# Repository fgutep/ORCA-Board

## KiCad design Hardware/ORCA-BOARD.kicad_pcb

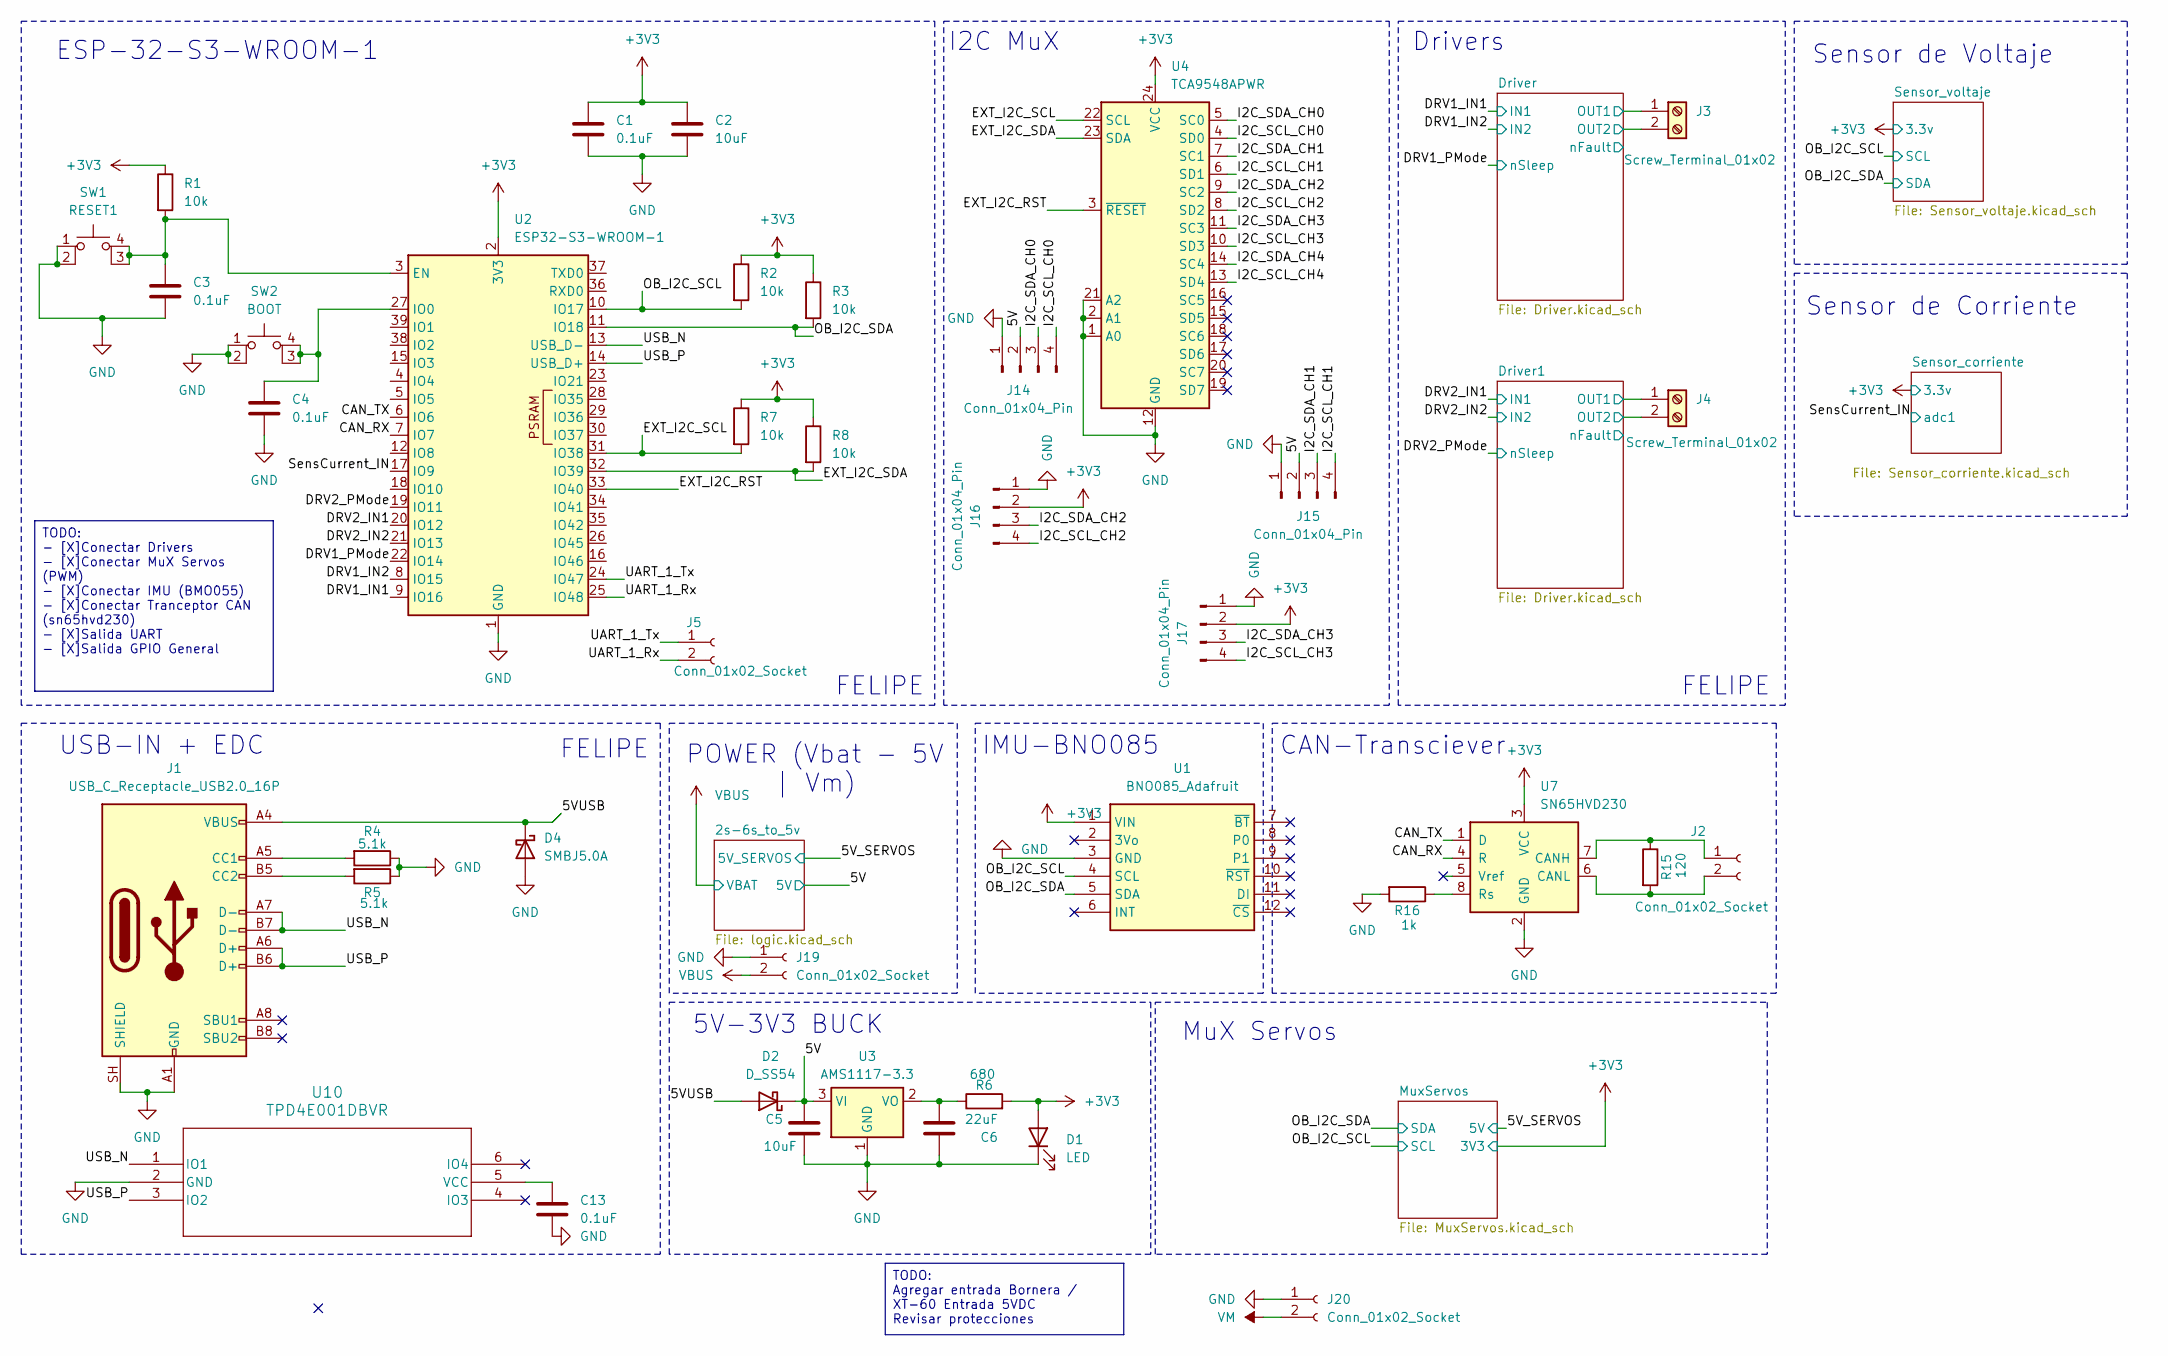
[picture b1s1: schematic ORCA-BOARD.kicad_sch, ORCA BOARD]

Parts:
C1, C3, C4, C13: 0.1uF; C_0603_1608Metric_Pad1.08x0.95mm_HandSolder
C2, C5: 10uF; C_1206_3216Metric_Pad1.33x1.80mm_HandSolder
C6: 22uF; C_1206_3216Metric_Pad1.33x1.80mm_HandSolder
D1: LED; LED_0603_1608Metric_Pad1.05x0.95mm_HandSolder
D2: D_SS54; D_SMA_Handsoldering
D4: SMBJ5.0A; D_SMB
J1: USB_C_Receptacle_USB2.0_16P; USB_C_Receptacle_GCT_USB4105-xx-A_16P_TopMnt_Horizontal
J2: Conn_01x02_Socket; JST_ZH_B2B-ZR_1x02_P1.50mm_Vertical
J3, J4: Screw_Terminal_01x02; TerminalBlock_Phoenix_MPT-0,5-2-2.54_1x02_P2.54mm_Horizontal
J5: Conn_01x02_Socket; JST_EH_B2B-EH-A_1x02_P2.50mm_Vertical
J14, J15, J16, J17: Conn_01x04_Pin; JST_EH_B4B-EH-A_1x04_P2.50mm_Vertical
J19, J20: Conn_01x02_Socket; AMASS_XT60-F_1x02_P7.20mm_Vertical
R1, R2, R3, R7, R8: 10k; LED_0603_1608Metric_Pad1.05x0.95mm_HandSolder
R4, R5: 5.1k; LED_0603_1608Metric_Pad1.05x0.95mm_HandSolder
R6: 680; LED_0603_1608Metric_Pad1.05x0.95mm_HandSolder
R15: 120; LED_0603_1608Metric_Pad1.05x0.95mm_HandSolder
R16: 1k; LED_0603_1608Metric_Pad1.05x0.95mm_HandSolder
SW1: RESET1; SW_SPST_B3S-1000_1_4_labels
SW2: BOOT; SW_SPST_B3S-1000_1_4_labels
U1: BNO085_Adafruit
U2: ESP32-S3-WROOM-1
U3: AMS1117-3.3; SOT-223-3_TabPin2
U4: TCA9548APWR; TSSOP-24_4.4x7.8mm_P0.65mm
U7: SN65HVD230; SOIC-8_3.9x4.9mm_P1.27mm
U10: TPD4E001DBVR; DBV6-M

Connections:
+3V3: C1.1, C2.1, D1.2 (A), J16.2, J17.2, R1.1, R2.1, R3.1, R6.2, R7.1, R8.1, U1.1 (VIN), U2.2 (3V3), U4.24 (VCC), U7.3 (VCC); also elsewhere on the board
/5V: C5.1, D2.1 (K), J14.2, J15.2, U3.3 (VI); also elsewhere on the board
/5VUSB: D2.2 (A), D4.1 (K), J1.A4 (VBUS), J1.A9 (VBUS), J1.B4 (VBUS), J1.B9 (VBUS)
/CAN_RX: U2.7 (IO7), U7.4 (R)
/CAN_TX: U2.6 (IO6), U7.1 (D)
/DRV1_IN1: U2.9 (IO16); also elsewhere on the board
/DRV1_IN2: U2.8 (IO15); also elsewhere on the board
/DRV1_PMode: U2.22 (IO14); also elsewhere on the board
/DRV2_IN1: U2.20 (IO12); also elsewhere on the board
/DRV2_IN2: U2.21 (IO13); also elsewhere on the board
/DRV2_PMode: U2.19 (IO11); also elsewhere on the board
/Driver1/OUT1: J4.1; also elsewhere on the board
/Driver1/OUT2: J4.2; also elsewhere on the board
/Driver/OUT1: J3.1; also elsewhere on the board
/Driver/OUT2: J3.2; also elsewhere on the board
/EXT_I2C_RST: U2.33 (IO40), U4.3 (~RESET)
/EXT_I2C_SCL: R7.2, U2.31 (IO38), U4.22 (SCL)
/EXT_I2C_SDA: R8.2, U2.32 (IO39), U4.23 (SDA)
/I2C_SCL_CH0: J14.4, U4.4 (SD0)
/I2C_SCL_CH1: J15.4, U4.6 (SD1)
/I2C_SCL_CH2: J16.4, U4.8 (SD2)
/I2C_SCL_CH3: J17.4, U4.10 (SD3)
/I2C_SCL_CH4: U4.13 (SD4)
/I2C_SDA_CH0: J14.3, U4.5 (SC0)
/I2C_SDA_CH1: J15.3, U4.7 (SC1)
/I2C_SDA_CH2: J16.3, U4.9 (SC2)
/I2C_SDA_CH3: J17.3, U4.11 (SC3)
/I2C_SDA_CH4: U4.14 (SC4)
/OB_I2C_SCL: R2.2, U1.4 (SCL), U2.10 (IO17); also elsewhere on the board
/OB_I2C_SDA: R3.2, U1.5 (SDA), U2.11 (IO18); also elsewhere on the board
/SensCurrent_IN: U2.17 (IO9); also elsewhere on the board
/UART_1_Rx: J5.2, U2.25 (IO48)
/UART_1_Tx: J5.1, U2.24 (IO47)
/USB_N: J1.A7 (D-), J1.B7 (D-), U2.13 (USB_D-), U10.1 (IO1)
/USB_P: J1.A6 (D+), J1.B6 (D+), U2.14 (USB_D+), U10.3 (IO2)
GND: C1.2, C2.2, C3.2, C4.1, C5.2, C6.1, C13.2, D1.1 (K), D4.2 (A), J1.A1 (GND), J1.A12 (GND), J1.B1 (GND), J1.B12 (GND), J1.SH (SHIELD), J14.1, J15.1, J16.1, J17.1, J19.1, J20.1, R4.1, R5.1, R16.2, SW1.1, SW1.2, SW2.1, SW2.2, U1.3 (GND), U2.1 (GND), U2.40 (GND), U2.41 (GND), U3.1 (GND), U4.1 (A0), U4.2 (A1), U4.12 (GND), U4.21 (A2), U7.2 (GND), U10.2 (GND); also elsewhere on the board
unnamed: J1.A5 (CC1), R4.2
unnamed: J1.B5 (CC2), R5.2
unnamed: J2.1, R15.1, U7.7 (CANH)
unnamed: J2.2, R15.2, U7.6 (CANL)
unnamed: C3.1, R1.2, SW1.3 (K), SW1.4 (A), U2.3 (EN)
unnamed: C4.2, SW2.3 (K), SW2.4 (A), U2.27 (IO0)
unnamed: C6.2, R6.1, U3.2 (VO)
unnamed: R16.1, U7.8 (Rs)
unnamed: C13.1, U10.5 (VCC)
VBUS: J19.2; also elsewhere on the board
VM: J20.2; also elsewhere on the board

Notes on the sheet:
FELIPE
Drivers
USB-IN + EDC
ESP-32-S3-WROOM-1
5V-3V3 BUCK
MuX Servos
Sensor de Corriente
I2C MuX
Sensor de Voltaje
POWER (Vbat - 5V | Vm)
CAN-Transciever
IMU-BNO085
TODO: Agregar entrada Bornera / XT-60 Entrada 5VDC Revisar protecciones
TODO: - [X]Conectar Drivers - [X]Conectar MuX Servos (PWM) - [X]Conectar IMU (BMO055) - [X]Conectar Tranceptor CAN (sn65hvd230) - [X]Salida UART - [X]Salida GPIO General

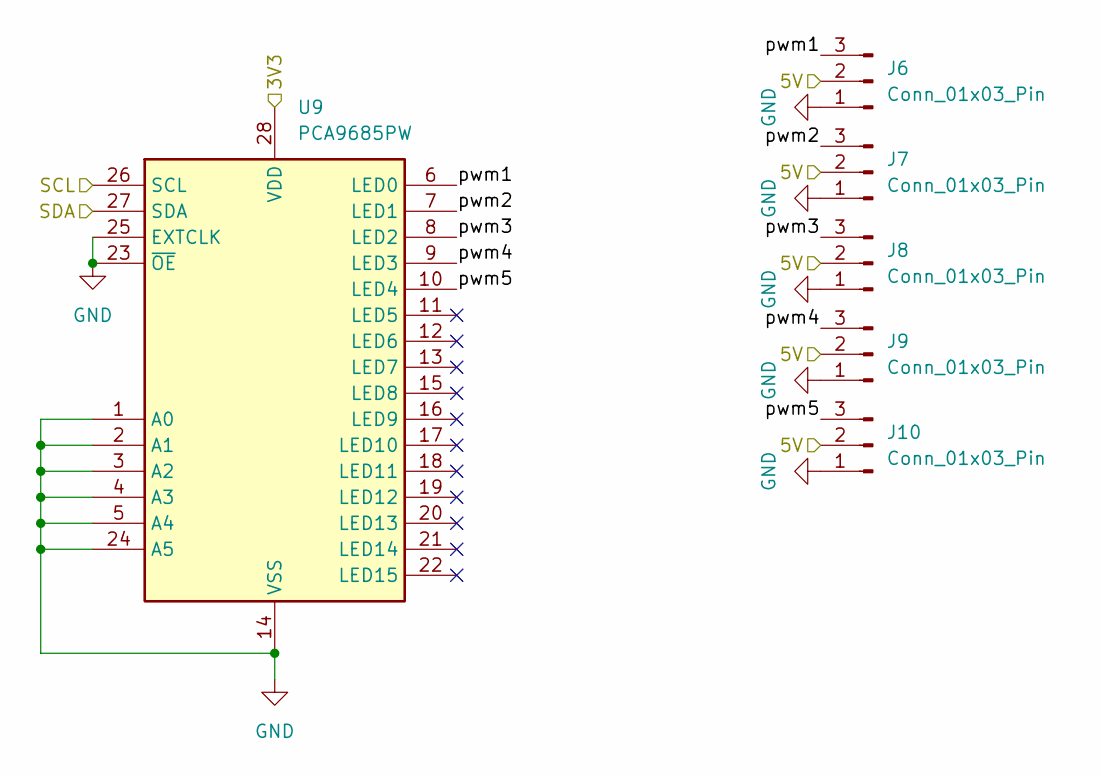
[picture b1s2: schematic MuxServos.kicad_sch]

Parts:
J6, J7, J8, J9, J10: Conn_01x03_Pin; PinHeader_1x03_P2.54mm_Vertical
U9: PCA9685PW; TSSOP-28_4.4x9.7mm_P0.65mm

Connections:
+3V3: U9.28 (VDD); also elsewhere on the board
/5V_SERVOS: J6.2, J7.2, J8.2, J9.2, J10.2; also elsewhere on the board
/MuxServos/pwm1: J6.3, U9.6 (LED0)
/MuxServos/pwm2: J7.3, U9.7 (LED1)
/MuxServos/pwm3: J8.3, U9.8 (LED2)
/MuxServos/pwm4: J9.3, U9.9 (LED3)
/MuxServos/pwm5: J10.3, U9.10 (LED4)
/OB_I2C_SCL: U9.26 (SCL); also elsewhere on the board
/OB_I2C_SDA: U9.27 (SDA); also elsewhere on the board
GND: J6.1, J7.1, J8.1, J9.1, J10.1, U9.1 (A0), U9.2 (A1), U9.3 (A2), U9.4 (A3), U9.5 (A4), U9.14 (VSS), U9.23 (~OE), U9.24 (A5), U9.25 (EXTCLK); also elsewhere on the board

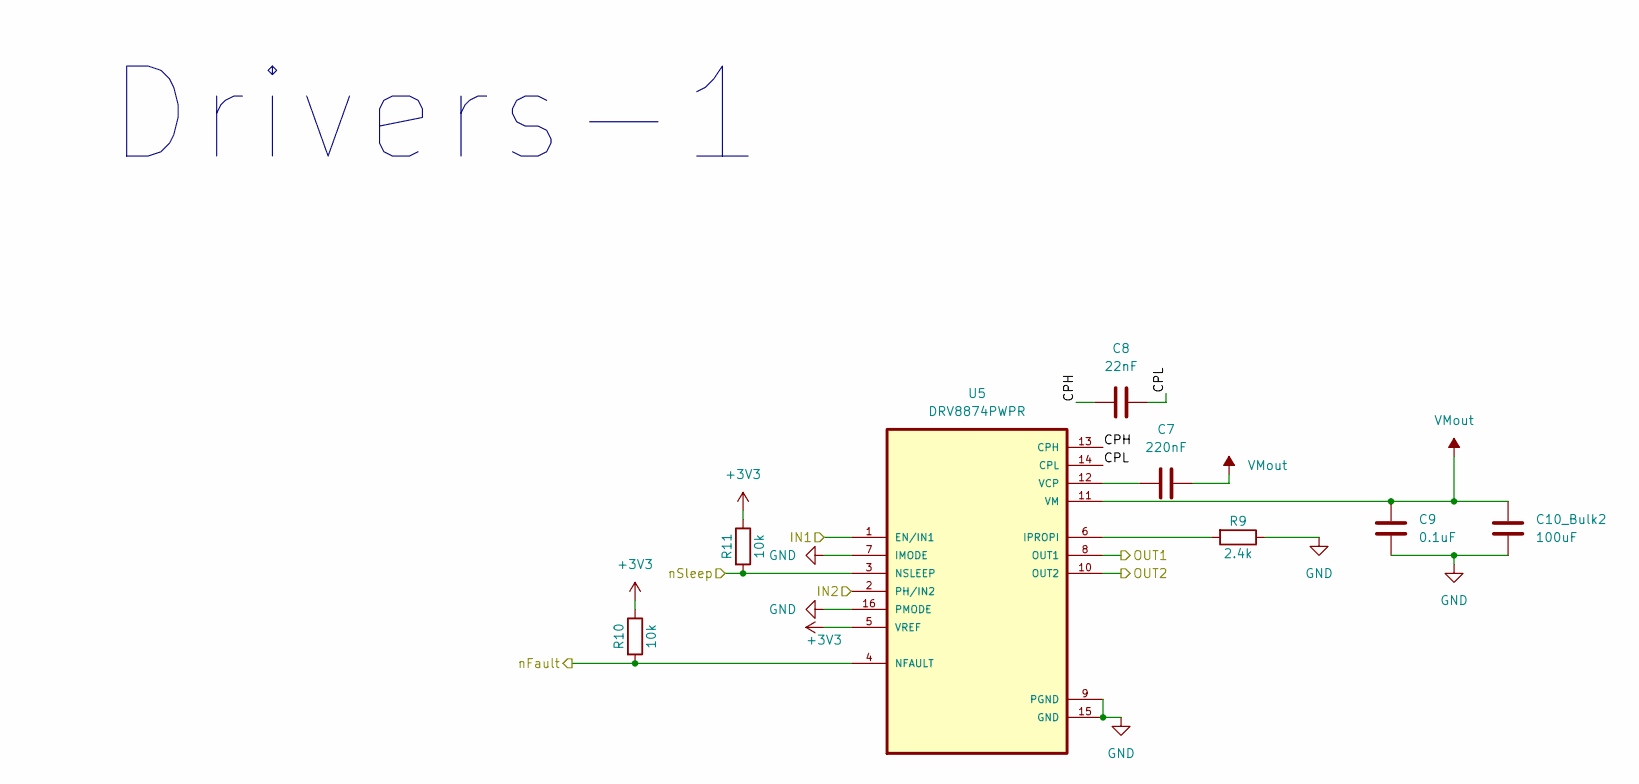
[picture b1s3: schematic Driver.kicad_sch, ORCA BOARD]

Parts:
C7: 220nF; C_0603_1608Metric_Pad1.08x0.95mm_HandSolder
C8: 22nF; C_0603_1608Metric_Pad1.08x0.95mm_HandSolder
C9: 0.1uF; C_0603_1608Metric_Pad1.08x0.95mm_HandSolder
C10_Bulk2: 100uF; CP_Elec_10x10.5
R9: 2.4k; R_0603_1608Metric_Pad0.98x0.95mm_HandSolder
R10, R11: 10k; R_0603_1608Metric_Pad0.98x0.95mm_HandSolder
U5: DRV8874PWPR; SOP65P640X120-17N

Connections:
+3V3: R10.1, R11.1, U5.5 (VREF); also elsewhere on the board
/DRV1_IN1: U5.1 (EN/IN1); also elsewhere on the board
/DRV1_IN2: U5.2 (PH/IN2); also elsewhere on the board
/DRV1_PMode: R11.2, U5.3 (NSLEEP); also elsewhere on the board
/Driver/CPH: C8.2, U5.13 (CPH)
/Driver/CPL: C8.1, U5.14 (CPL)
/Driver/OUT1: U5.8 (OUT1); also elsewhere on the board
/Driver/OUT2: U5.10 (OUT2); also elsewhere on the board
/Driver/nFault: R10.2, U5.4 (NFAULT)
GND: C9.2, C10_Bulk2.2, R9.1, U5.7 (IMODE), U5.9 (PGND), U5.15 (GND), U5.16 (PMODE); also elsewhere on the board
unnamed: R9.2, U5.6 (IPROPI)
unnamed: C7.1, U5.12 (VCP)
VMout: C7.2, C9.1, C10_Bulk2.1, U5.11 (VM); also elsewhere on the board

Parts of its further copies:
C10: 22nF; C_0603_1608Metric_Pad1.08x0.95mm_HandSolder
C10_Bulk1: 100uF; CP_Elec_10x10.5
C11: 220nF; C_0603_1608Metric_Pad1.08x0.95mm_HandSolder
C12: 0.1uF; C_0603_1608Metric_Pad1.08x0.95mm_HandSolder
R12, R13: 10k; R_0603_1608Metric_Pad0.98x0.95mm_HandSolder
R14: 2.4k; R_0603_1608Metric_Pad0.98x0.95mm_HandSolder
U6: DRV8874PWPR; SOP65P640X120-17N

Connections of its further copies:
+3V3: R12.1, R13.1, U6.5 (VREF); also elsewhere on the board
/DRV2_IN1: U6.1 (EN/IN1); also elsewhere on the board
/DRV2_IN2: U6.2 (PH/IN2); also elsewhere on the board
/DRV2_PMode: R13.2, U6.3 (NSLEEP); also elsewhere on the board
/Driver1/CPH: C10.2, U6.13 (CPH)
/Driver1/CPL: C10.1, U6.14 (CPL)
/Driver1/OUT1: U6.8 (OUT1); also elsewhere on the board
/Driver1/OUT2: U6.10 (OUT2); also elsewhere on the board
/Driver1/nFault: R12.2, U6.4 (NFAULT)
GND: C10_Bulk1.2, C12.2, R14.1, U6.7 (IMODE), U6.9 (PGND), U6.15 (GND), U6.16 (PMODE); also elsewhere on the board
unnamed: R14.2, U6.6 (IPROPI)
unnamed: C11.1, U6.12 (VCP)
VMout: C10_Bulk1.1, C11.2, C12.1, U6.11 (VM); also elsewhere on the board

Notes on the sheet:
Drivers-1

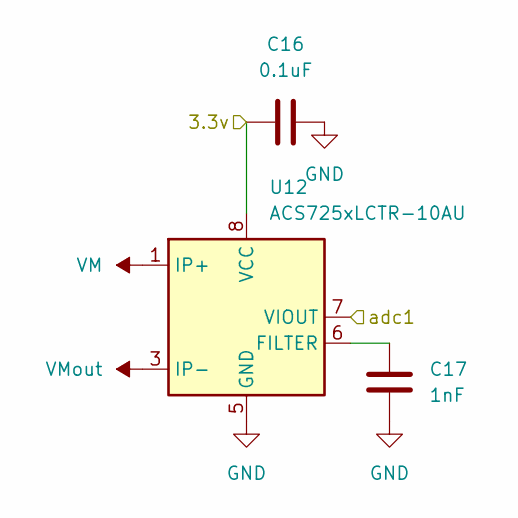
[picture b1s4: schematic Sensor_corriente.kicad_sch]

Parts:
C16: 0.1uF; C_0603_1608Metric_Pad1.08x0.95mm_HandSolder
C17: 1nF; C_0603_1608Metric_Pad1.08x0.95mm_HandSolder
U12: ACS725xLCTR-10AU; SOIC-8_3.9x4.9mm_P1.27mm

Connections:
+3V3: C16.1, U12.8 (VCC); also elsewhere on the board
/SensCurrent_IN: U12.7 (VIOUT); also elsewhere on the board
GND: C16.2, C17.2, U12.5 (GND); also elsewhere on the board
unnamed: C17.1, U12.6 (FILTER)
VM: U12.1 (IP+), U12.2 (IP+); also elsewhere on the board
VMout: U12.3 (IP-), U12.4 (IP-); also elsewhere on the board

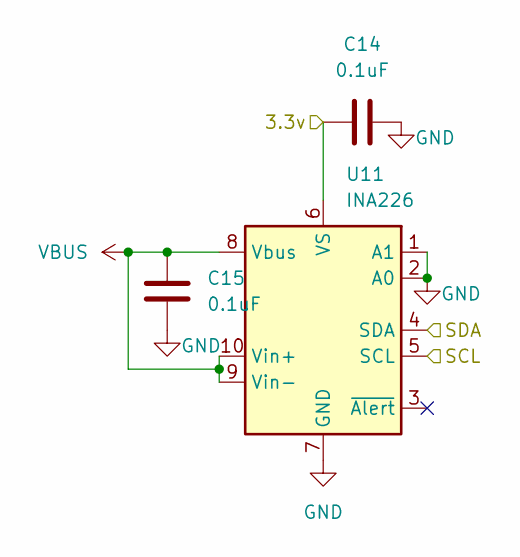
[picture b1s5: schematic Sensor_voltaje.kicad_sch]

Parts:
C14, C15: 0.1uF; C_0603_1608Metric_Pad1.08x0.95mm_HandSolder
U11: INA226; TSSOP-10_3x3mm_P0.5mm

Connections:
+3V3: C14.1, U11.6 (VS); also elsewhere on the board
/OB_I2C_SCL: U11.5 (SCL); also elsewhere on the board
/OB_I2C_SDA: U11.4 (SDA); also elsewhere on the board
GND: C14.2, C15.1, U11.1 (A1), U11.2 (A0), U11.7 (GND); also elsewhere on the board
VBUS: C15.2, U11.8 (Vbus), U11.9 (Vin-), U11.10 (Vin+); also elsewhere on the board

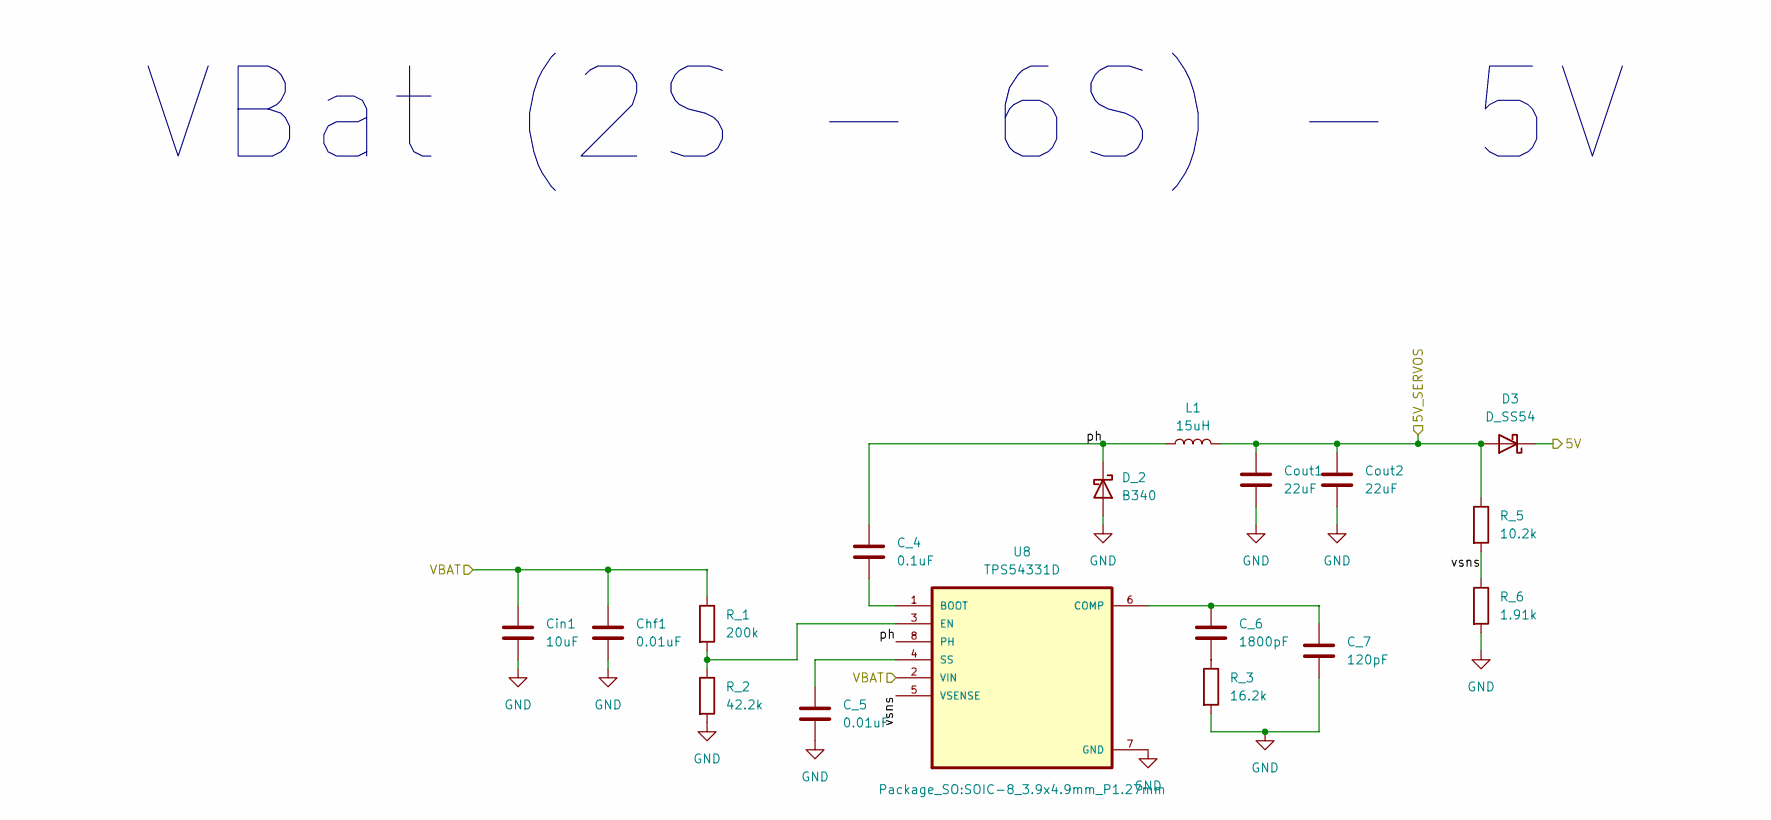
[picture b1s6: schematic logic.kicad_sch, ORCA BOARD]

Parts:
C_4: 0.1uF; C_0603_1608Metric_Pad1.08x0.95mm_HandSolder
C_5: 0.01uF; C_0603_1608Metric_Pad1.08x0.95mm_HandSolder
C_6: 1800pF; C_0603_1608Metric_Pad1.08x0.95mm_HandSolder
C_7: 120pF; C_0603_1608Metric_Pad1.08x0.95mm_HandSolder
Chf1: 0.01uF; C_0603_1608Metric_Pad1.08x0.95mm_HandSolder
Cin1: 10uF; C_1206_3216Metric_Pad1.33x1.80mm_HandSolder
Cout1, Cout2: 22uF; C_1206_3216Metric_Pad1.33x1.80mm_HandSolder
D3: D_SS54; D_SMA_Handsoldering
D_2: B340; D_SMC
L1: 15uH; L_7.3x7.3_H3.5
R_1: 200k; R_0603_1608Metric_Pad0.98x0.95mm_HandSolder
R_2: 42.2k; R_0603_1608Metric_Pad0.98x0.95mm_HandSolder
R_3: 16.2k; R_0603_1608Metric_Pad0.98x0.95mm_HandSolder
R_5: 10.2k; R_0603_1608Metric_Pad0.98x0.95mm_HandSolder
R_6: 1.91k; R_0603_1608Metric_Pad0.98x0.95mm_HandSolder
U8: TPS54331D; SOIC-8_3.9x4.9mm_P1.27mm

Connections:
/2s-6s_to_5v/ph: C_4.1, D_2.1 (K), L1.1, U8.8 (PH)
/2s-6s_to_5v/vsns: R_5.2, R_6.1, U8.5 (VSENSE)
/5V: D3.1 (K); also elsewhere on the board
/5V_SERVOS: Cout1.1, Cout2.1, D3.2 (A), L1.2, R_5.1; also elsewhere on the board
GND: C_5.2, C_7.2, Chf1.2, Cin1.2, Cout1.2, Cout2.2, D_2.2 (A), R_2.2, R_3.2, R_6.2, U8.7 (GND); also elsewhere on the board
unnamed: C_6.2, R_3.1
unnamed: C_4.2, U8.1 (BOOT)
unnamed: C_6.1, C_7.1, U8.6 (COMP)
unnamed: R_1.2, R_2.1, U8.3 (EN)
unnamed: C_5.1, U8.4 (SS)
VBUS: Chf1.1, Cin1.1, R_1.1, U8.2 (VIN); also elsewhere on the board

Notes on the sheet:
VBat (2S - 6S) - 5V

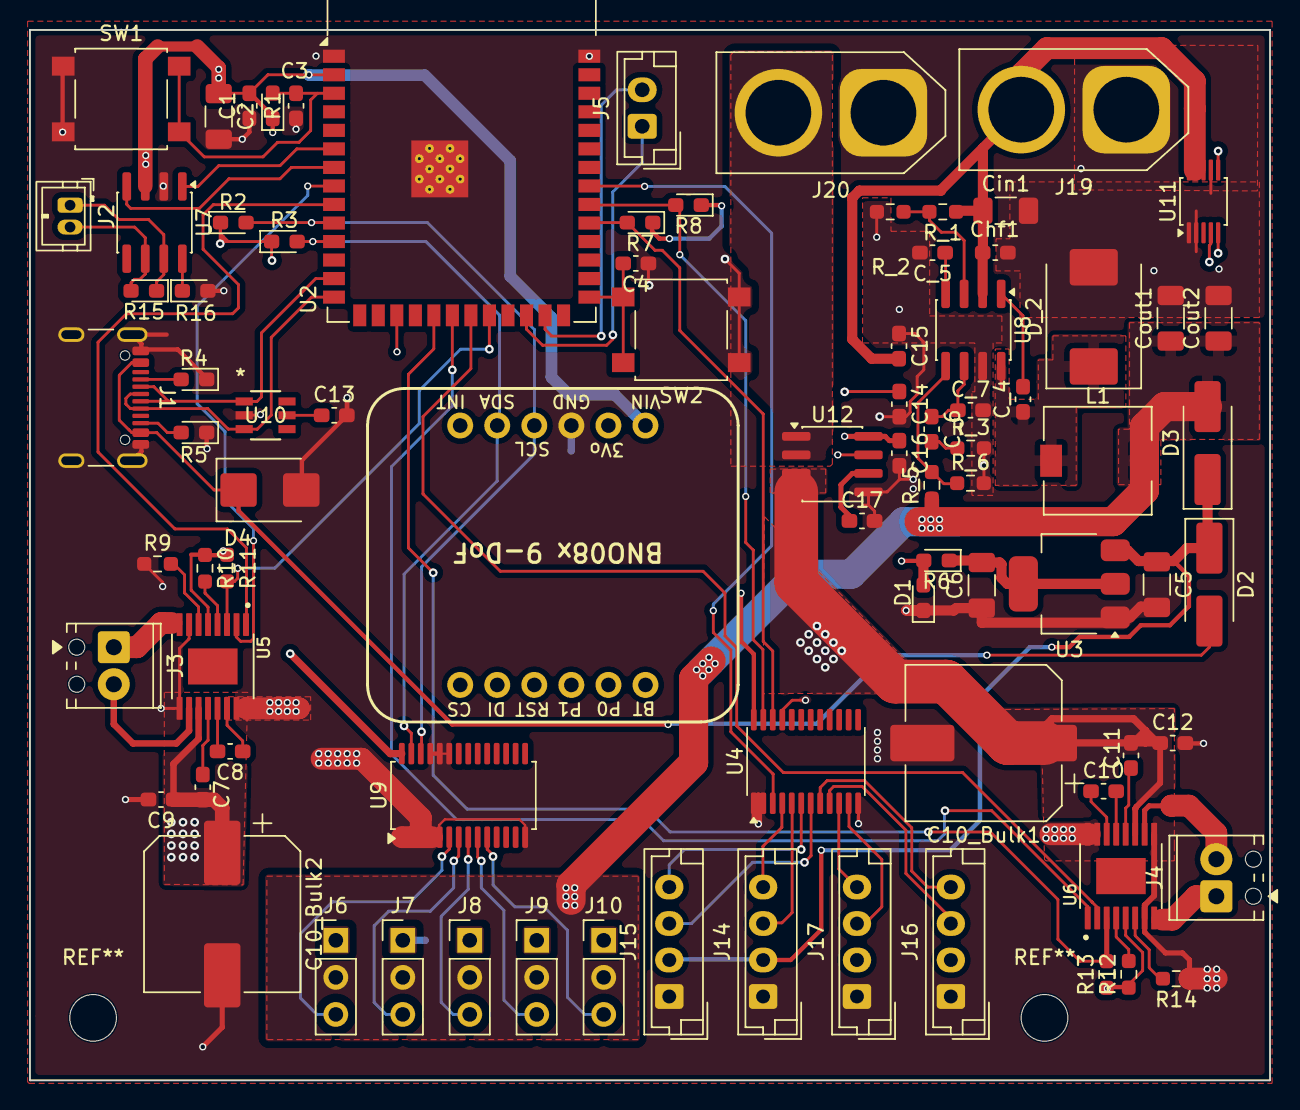
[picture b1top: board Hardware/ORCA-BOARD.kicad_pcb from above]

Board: 4 copper layers, 85.0 x 72.0 mm, 84 parts (0 on the bottom side), 70 nets.

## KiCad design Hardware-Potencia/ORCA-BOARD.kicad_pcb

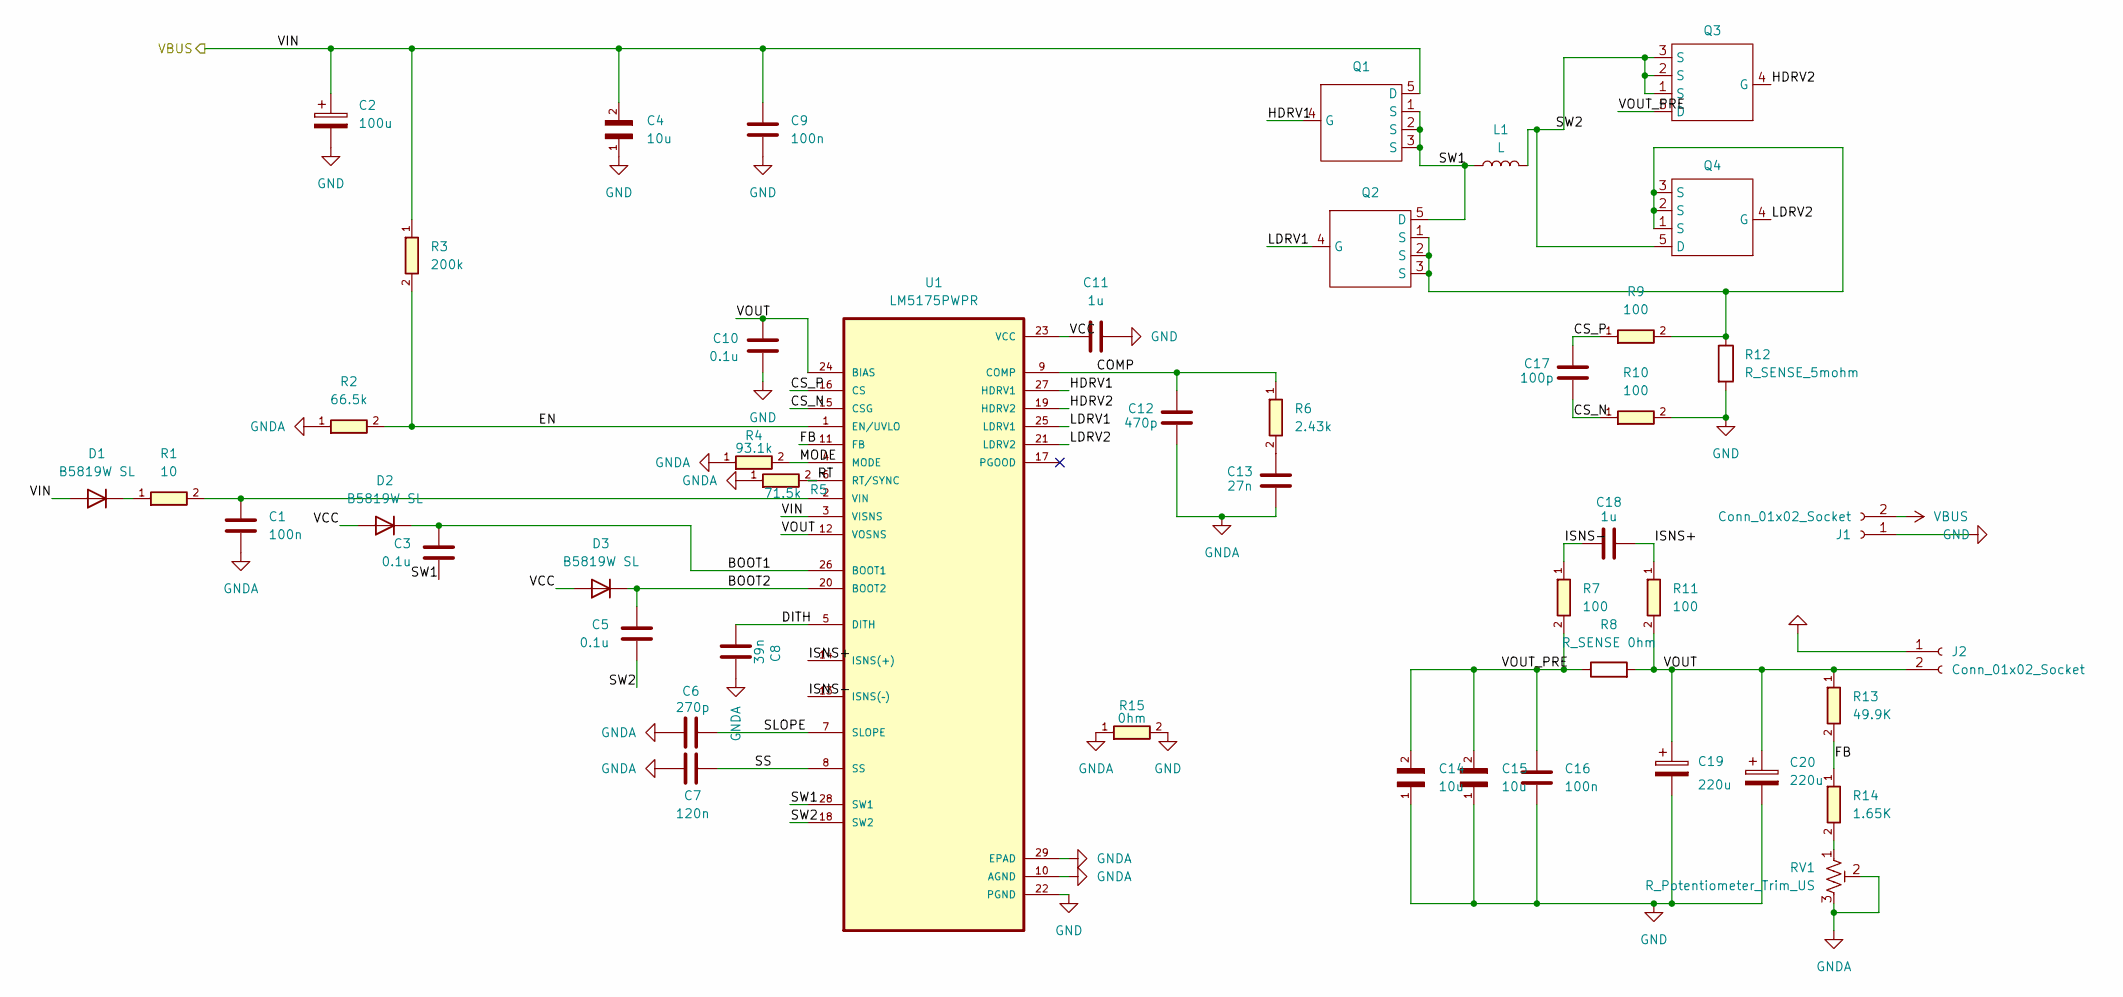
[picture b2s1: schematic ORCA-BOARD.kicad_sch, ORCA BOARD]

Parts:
C1: 100n; 0603
C2: 100u; CP_Radial_D8.0mm_P3.50mm
C3, C5, C10: 0.1u; 0603
C4, C14, C15: 10u; CAPC3225X280N
C6: 270p; 0603
C7: 120n; 0603
C8: 39n; 0603
C9, C16: 100n; CAPC3225X280N
C11, C18: 1u; CAPC2012X100N
C12: 470p; 0603
C13: 27n; 0603
C17: 100p; 0603
C19, C20: 220u; CP_Radial_D8.0mm_P3.50mm
D1, D2, D3: B5819W SL; D_SOD-123
J1, J2: Conn_01x02_Socket; AMASS_XT60-F_1x02_P7.20mm_Vertical
L1: L; L_Pulse_PA4344
Q1, Q2, Q3, Q4: LFPAK56
R1: 10; 0603
R2: 66.5k; 0603
R3: 200k; 0603
R4: 93.1k; 0603
R5: 71.5k; 0603
R6: 2.43k; 0603
R7, R9, R10, R11: 100; 0603
R8: R_SENSE 0hm; RES_1-2176421-2
R12: R_SENSE_5mohm; R_2512_Kelvin_TLRP
R13: 49.9K; 0603
R14: 1.65K; 0603
R15: 0hm; 0603
RV1: R_Potentiometer_Trim_US; Potentiometer_Bourns_3296W_Vertical
U1: LM5175PWPR; LM5175PWP

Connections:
/BOOT1: C3.1, D2.1 (K), U1.26 (BOOT1)
/BOOT2: C5.1, D3.1 (K), U1.20 (BOOT2)
/COMP: C12.2, R6.1, U1.9 (COMP)
/CS_N: C17.1, R10.1, U1.15 (CSG)
/CS_P: C17.2, R9.1, U1.16 (CS)
/DITH: C8.2, U1.5 (DITH)
/EN: R2.2, R3.2, U1.1 (EN/UVLO)
/FB: R13.2, R14.1, U1.11 (FB)
/HDRV1: Q1.4 (G), U1.27 (HDRV1)
/HDRV2: Q3.4 (G), U1.19 (HDRV2)
/ISNS+: C18.2, R11.1, U1.14 (ISNS(+))
/ISNS-: C18.1, R7.1, U1.13 (ISNS(–))
/LDRV1: Q2.4 (G), U1.25 (LDRV1)
/LDRV2: Q4.4 (G), U1.21 (LDRV2)
/MODE: R4.2, U1.4 (MODE)
/RT: R5.2, U1.6 (RT/SYNC)
/SLOPE: C6.2, U1.7 (SLOPE)
/SS: C7.2, U1.8 (SS)
/SW1: C3.2, L1.1, Q1.1 (S), Q1.2 (S), Q1.3 (S), Q2.5 (D), U1.28 (SW1)
/SW2: C5.2, L1.2, Q3.1 (S), Q3.2 (S), Q3.3 (S), Q4.5 (D), U1.18 (SW2)
/VCC: C11.1, D2.2 (A), D3.2 (A), U1.23 (VCC)
/VOUT: C10.1, C19.1, C20.1, J2.2, R8.2, R11.2, R13.1, U1.12 (VOSNS), U1.24 (BIAS)
/VOUT_PRE: C14.2, C15.2, C16.1, Q3.5 (D), R7.2, R8.1
GND: C2.2, C4.1, C9.2, C10.2, C11.2, C14.1, C15.1, C16.2, C19.2, C20.2, J1.1, J2.1, R10.2, R12.2, R15.2, U1.22 (PGND)
GNDA: C1.2, C6.1, C7.1, C8.1, C12.1, C13.1, R2.1, R4.1, R5.1, R15.1, RV1.2, RV1.3, U1.10 (AGND), U1.29 (EPAD)
unnamed: C13.2, R6.2
unnamed: D1.1 (K), R1.1
unnamed: Q2.1 (S), Q2.2 (S), Q2.3 (S), Q4.1 (S), Q4.2 (S), Q4.3 (S), R9.2, R12.1
unnamed: R14.2, RV1.1
unnamed: C1.1, R1.2, U1.2 (VIN)
VBUS: C2.1, C4.2, C9.1, D1.2 (A), J1.2, Q1.5 (D), R3.1, U1.3 (VISNS)

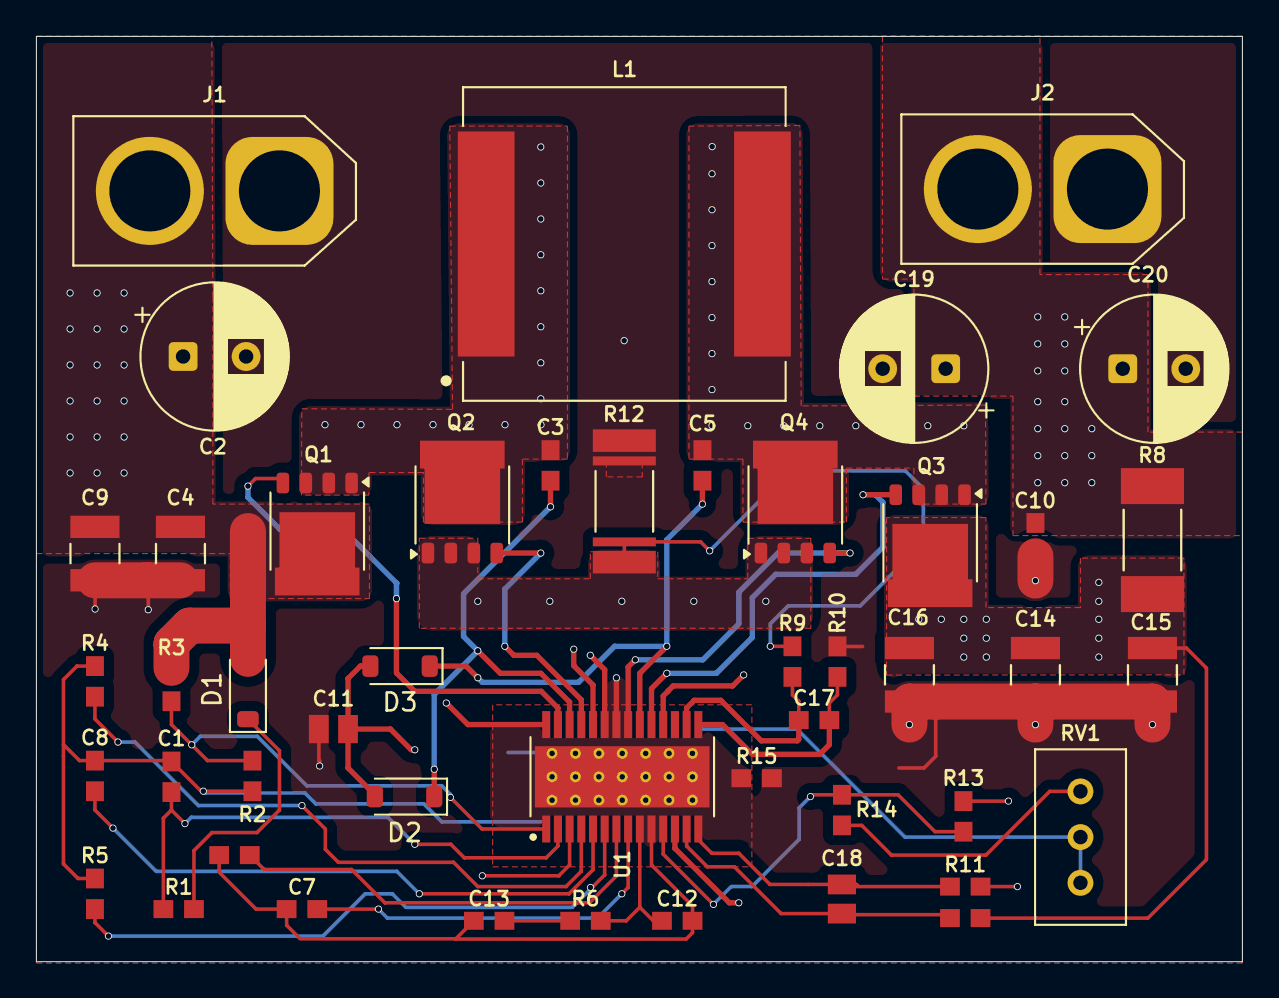
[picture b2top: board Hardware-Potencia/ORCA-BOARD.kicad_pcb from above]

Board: 4 copper layers, 67.0 x 51.4 mm, 47 parts (0 on the bottom side), 31 nets.
